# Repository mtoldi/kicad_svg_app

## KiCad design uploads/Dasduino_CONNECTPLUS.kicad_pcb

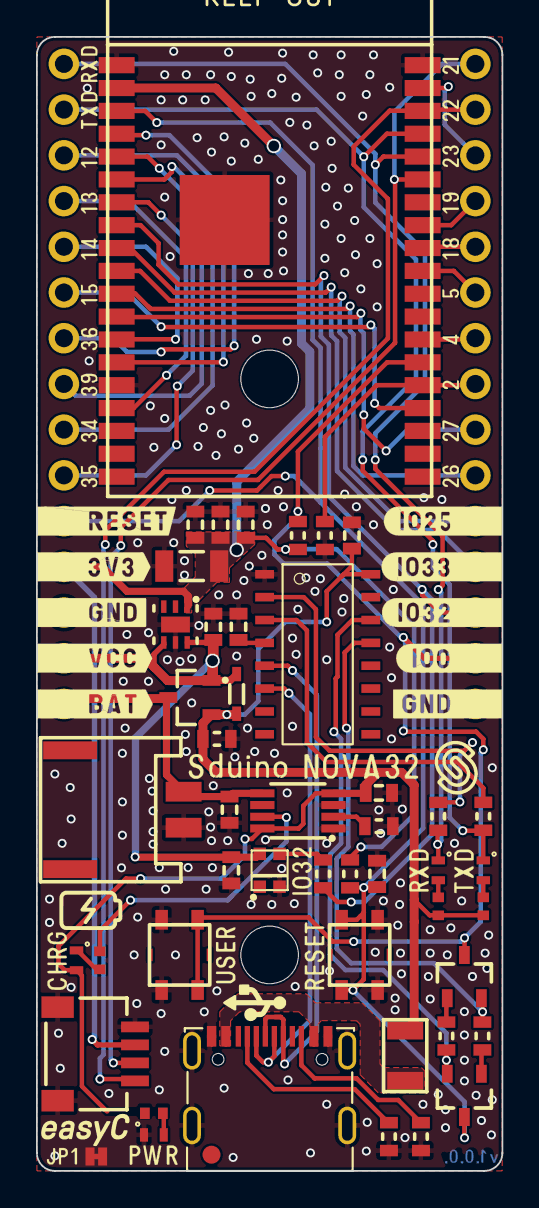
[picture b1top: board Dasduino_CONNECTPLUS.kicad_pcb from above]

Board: 2 copper layers, 25.9 x 63.0 mm, 51 parts (0 on the bottom side), 49 nets.

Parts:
C1: 10uF; 1206C
C2, C5, C11: 1uF; 0603C
C3, C4, C6: 0.1uF; 0603C
C7, C8, C9, C10: 2.2uF; 0603C
D1: blue; 0402LED
D2: orange; 0402LED
D3: purple; 0402LED
D4: WS2812B-2020
D5: schottky diode; SOD-323
D6: red; 0402LED
F1: 1206FUSE-500mA; 1206FUSE
FD1: Fiducial_Stencil; FIDUCIAL_1MM_PASTE
H1, H3: HOLE_3.2mm
K1: U262-161N-4BVC11
K2: easyC-SMD; easyC-connector
K3: JST-2pin-SMD
K4, K5: HEADER_MALE_15X1
Q1: PMOS-SOT-23-3; SOT-23-3
Q2, Q3: NPN-SOT-23-3; SOT-23-3
R1, R12, R13: 10k; 0603R
R2, R3: 5.1k; 0603R
R4, R5, R17: 1k; 0603R
R6, R7, R8, R15: 0R; 0402R
R9, R10, R11: 0603R
R14: 3k; 0603R
SW1, SW2: YTSA007A0151803B
U1: CH340C; SOP-16
U2: ESP32-WROVER
U3: TPS7A2633DRVR
U4: TP4056M; TP4056M-MSOP8

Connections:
+3V3: C1.2, C5.2, C6.2, C8.2, K2.3 (3V3), K4.4, R1.2, R13.2, U2.2 (VDD33), U3.1 (OUT)
D+: K1.A6 (DP1), K1.B6 (DP2), U1.5 (UD+)
D-: K1.A7 (DN1), K1.B7 (DN2), U1.6 (UD-)
DTR: Q3.2 (E), R10.1, U1.13 (DTR#)
GND: C1.1, C2.1, C3.1, C4.2, C5.1, C6.1, C7.1, C8.1, C9.1, C10.1, C11.2, D3.2 (K), D4.2 (GND), K1.A1 (GND), K1.A12 (GND), K1.B1 (GND), K1.B12 (GND), K1.SH (SHIELD), K2.4 (GND), K2.5 (SHIELD), K3.2 (-), K4.3, K5.1, R2.2, R3.2, R9.1, R12.1, R14.2, SW1.2, SW2.1, U1.1 (GND), U2.1 (GND), U2.15 (GND), U2.38 (GND), U2.39 (GND), U3.5 (GND), U4.1 (TEMP), U4.3 (GND)
IO0: K5.2, Q3.3 (C), R13.1, SW2.2, U2.25 (IO0)
IO2: K5.8, R12.2, U2.24 (IO2)
IO4: K5.9, U2.26 (IO4)
IO5: K5.10, U2.29 (IO5)
IO18: K5.11, U2.30 (IO18)
IO19: K5.12, U2.31 (IO19)
IO23: K5.13, U2.37 (IO23)
IO25: K5.5, U2.10 (IO25)
IO26: K5.6, U2.11 (IO26)
IO27: K5.7, U2.12 (IO27)
IO32: K5.3, R17.1, U2.8 (IO32)
IO33: K5.4, U2.9 (IO33)
IO34: K4.7, U2.6 (IO34)
IO35: K4.6, U2.7 (IO35)
unnamed: C4.1, U1.4 (V3)
unnamed: D1.1 (A), R6.1
unnamed: D2.1 (A), R7.1
unnamed: D3.1 (A), R8.2
unnamed: D4.3 (DI), R17.2
unnamed: D6.2 (K), R15.2
unnamed: F1.2, K1.A4 (VBUS), K1.A9 (VBUS), K1.B4 (VBUS), K1.B9 (VBUS)
unnamed: K1.A5 (CC1), R3.1
unnamed: K1.B5 (CC2), R2.1
unnamed: Q2.1 (B), R10.2
unnamed: Q3.1 (B), R11.2
unnamed: R4.1, U1.2 (TXD)
unnamed: R5.1, U1.3 (RXD)
unnamed: R14.1, U4.2 (PROG)
unnamed: R15.1, U4.7 (~CHRG)
RESET: C2.2, K4.5, Q2.3 (C), R1.1, SW1.1, U2.3 (EN)
RTS: Q2.2 (E), R11.1, U1.14 (RTS#)
RXD0: D2.2 (K), K4.15, R4.2, U2.34 (RXD0)
SCL: K2.1 (SCL), K5.14, U2.36 (IO22)
SDA: K2.2 (SDA), K5.15, U2.33 (IO21)
SENSOR_VN: K4.8, U2.5 (SENSOR_VN)
SENSOR_VP: K4.9, U2.4 (SENSOR_VP)
SPI_CS: K4.10, U2.23 (IO15)
SPI_MISO: K4.13, U2.14 (IO12)
SPI_MOSI: K4.12, U2.16 (IO13)
SPI_SCK: K4.11, U2.13 (IO14)
TXD0: D1.2 (K), K4.14, R5.2, U2.35 (TXD0)
VBAT: C9.2, K3.1 (+), K4.1, Q1.3 (D), U4.5 (BAT)
VCC: C7.2, C11.1, D4.4 (VDD), D5.2 (K), K4.2, Q1.2 (S), U3.4 (EN), U3.6 (IN)
VUSB: C3.2, C10.2, D5.1 (A), D6.1 (A), F1.1, Q1.1 (G), R6.2, R7.2, R8.1, R9.2, U1.16 (VCC), U4.4 (VCC), U4.8 (CE)

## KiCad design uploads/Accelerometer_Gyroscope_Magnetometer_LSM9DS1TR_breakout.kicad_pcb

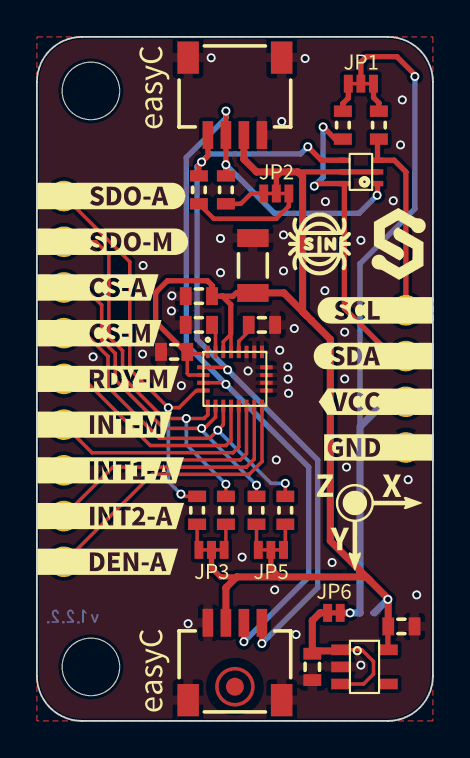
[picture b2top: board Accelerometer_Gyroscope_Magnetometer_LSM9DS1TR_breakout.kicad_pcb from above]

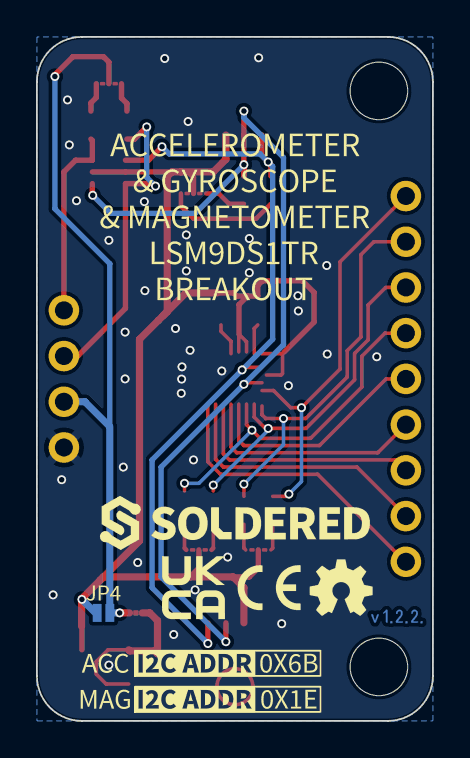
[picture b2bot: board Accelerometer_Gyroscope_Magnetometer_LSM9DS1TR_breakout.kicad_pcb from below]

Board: 2 copper layers, 22.0 x 38.0 mm, 59 parts (13 on the bottom side), 27 nets.

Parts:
C1, C2, C5: 100n; 0603C
C3: 10u; 1206C
C4: 10n; 0603C
C6, C7: 2u2; 0603C
FD1: FIDUCIAL; FIDUCIAL_23
H1, H2: HOLE_3.2mm
JP1, JP2, JP3, JP5: SMD_JUMPER_3_PAD_TRACE
JP4: SMD_JUMPER
JP6: SMD-JUMPER-CONNECTED_TRACE_SLODERMASK
K1: HEADER_MALE_9X1
K2, K4: easyC-SMD; easyC-connector
K3: HEADER_MALE_4X1
R1, R2, R3, R4, R5, R6, R7, R8: 10k; 0603R
U1: NMOS-DUAL; SOT-363
U2: LSM9DS1TR
U3: SE5218; SOT-23-5
kibuzzard-646B23F4: G***; kibuzzard-646B23F4
kibuzzard-6411B0B5: G***; kibuzzard-6411B0B5
kibuzzard-6411B0E0: G***; kibuzzard-6411B0E0
kibuzzard-6411B0F4: G***; kibuzzard-6411B0F4
kibuzzard-6411B1B6: G***; kibuzzard-6411B1B6
kibuzzard-6411B1E2: G***; kibuzzard-6411B1E2
kibuzzard-6411B1FF: G***; kibuzzard-6411B1FF
kibuzzard-6411B2B7: G***; kibuzzard-6411B2B7
kibuzzard-6411B2D2: G***; kibuzzard-6411B2D2
kibuzzard-6411B06B: G***; kibuzzard-6411B06B
kibuzzard-6411B07F: G***; kibuzzard-6411B07F
kibuzzard-6411B21F: G***; kibuzzard-6411B21F
kibuzzard-6411B22F: G***; kibuzzard-6411B22F
kibuzzard-6411B25F: G***; kibuzzard-6411B25F
kibuzzard-6411B32F: G***; kibuzzard-6411B32F
kibuzzard-6411B33C: G***; kibuzzard-6411B33C
kibuzzard-6411B059: G***; kibuzzard-6411B059
kibuzzard-6411B061: G***; kibuzzard-6411B061
kibuzzard-6411B074: G***; kibuzzard-6411B074
kibuzzard-6411B103: G***; kibuzzard-6411B103
kibuzzard-6411B119: G***; kibuzzard-6411B119
kibuzzard-6411B182: G***; kibuzzard-6411B182
kibuzzard-6411B196: G***; kibuzzard-6411B196
kibuzzard-6411B241: G***; kibuzzard-6411B241
kibuzzard-6411B292: G***; kibuzzard-6411B292
kibuzzard-6411B295: G***; kibuzzard-6411B295
kibuzzard-6411B327: G***; kibuzzard-6411B327
kibuzzard-6411B347: G***; kibuzzard-6411B347

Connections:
3V3: C1.2, C3.1, C5.2, C7.2, JP2.2, JP3.2, JP4.2, JP5.2, K2.3 (3V3), K4.3 (3V3), U1.2 (G2), U1.5 (G1), U2.1 (VDDIO), U2.3 (VDDIO), U2.22 (VDD), U2.23 (VDD), U3.5 (VOUT)
5V: JP1.2, JP4.1, JP6.2, K3.2
CS_AG: K1.3, R7.1, U2.7 (CS_AG)
CS_M: K1.4, R8.1, U2.8 (CS_M)
DEN_AG: K1.9, U2.13 (DEN_AG)
DRDY_M: K1.5, U2.9 (DRDY_M)
GND: C1.1, C2.2, C3.2, C4.2, C5.1, C6.1, C7.1, K2.4 (GND), K2.5 (SHIELD), K3.1, K4.4 (GND), K4.5 (SHIELD), U2.14 (RES), U2.15 (RES), U2.16 (RES), U2.17 (RES), U2.18 (RES), U2.19 (GND), U2.20 (GND), U3.2 (GND)
INT1_AG: K1.7, U2.11 (INT1_AG)
INT2_AG: K1.8, U2.12 (INT2_AG)
INT_M: K1.6, U2.10 (INT_M)
unnamed: C2.1, U2.24 (C1)
unnamed: C4.1, U2.21 (CAP)
unnamed: C6.2, JP6.1, U3.1 (VIN), U3.3 (EN)
unnamed: JP3.1, R6.2
unnamed: JP3.3, R5.2
unnamed: JP5.1, R8.2
unnamed: JP5.3, R7.2
SCL3,3: K2.1 (SCL), K4.1 (SCL), R4.1, U1.4 (S1), U2.2 (SCL)
SCL5: K3.4, R2.2, U1.3 (D1)
SCL_PULL3,3: JP2.1, R4.2
SCL_PULL5: JP1.1, R2.1
SDA3,3: K2.2 (SDA), K4.2 (SDA), R1.2, U1.1 (S2), U2.4 (SDA)
SDA5: K3.3, R3.1, U1.6 (D2)
SDA_PULL3,3: JP2.3, R1.1
SDA_PULL5: JP1.3, R3.2
SDO_AG: K1.1, R5.1, U2.5 (SDO_AG)
SDO_M: K1.2, R6.1, U2.6 (SDO_M)

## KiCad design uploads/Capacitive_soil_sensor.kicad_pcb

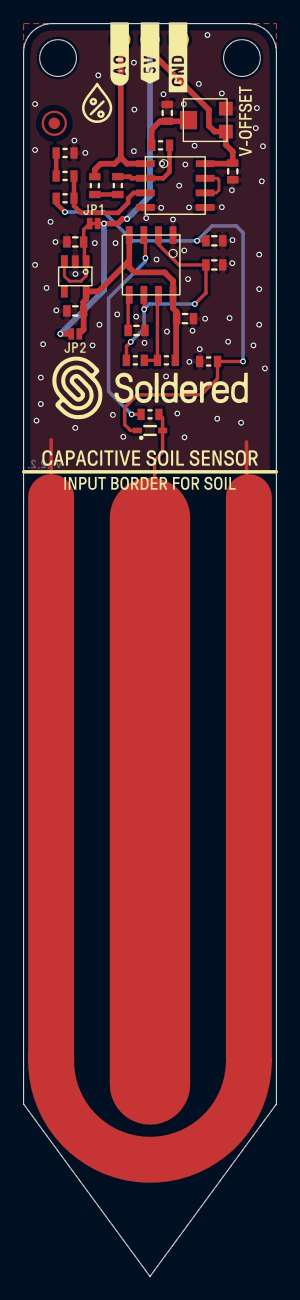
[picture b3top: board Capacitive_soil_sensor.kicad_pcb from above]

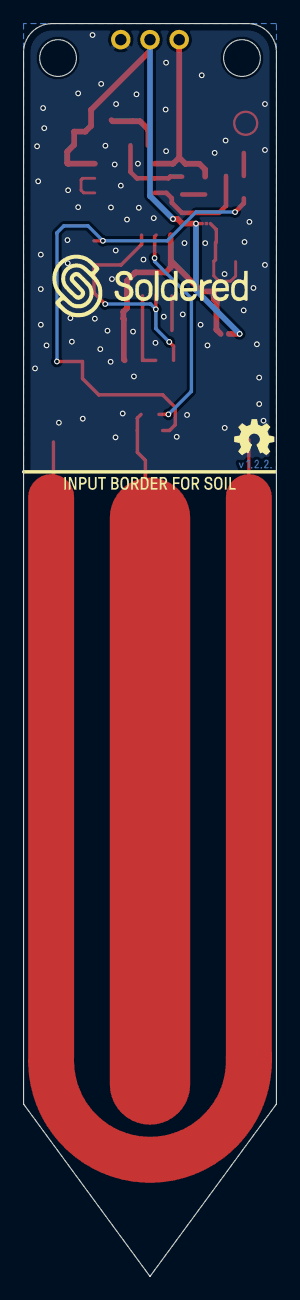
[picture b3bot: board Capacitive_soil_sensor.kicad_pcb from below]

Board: 2 copper layers, 22.0 x 109.0 mm, 33 parts (2 on the bottom side), 17 nets.

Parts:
C1: 1uF; 0603C
C2: 10nF; 0603C
C3: 0.01uF; 0603C
C4: 470pF; 0603C
C5, C6: 2.2uF; 0603C
C7, C8: 100n; 0603C
D1: BAT20J; SOD-323
FD1: FIDUCIAL; FIDUCIAL_23
H1, H2: HOLE_3.2mm
JP1: SMD-JUMPER-CONNECTED_TRACE_SLODERMASK
JP2: SMD_JUMPER
K1: HEADER_MALE_3X1
R1: 1M; 0603R
R2: 10K; 0603R
R3: 330R; 0603R
R4: 1K6; 0603R
R5, R9: 10k; 0603R
R6, R11: 47k; 0603R
R7, R10: 100k; 0603R
R8: tc33x-2-103e
U1: TLC555; SOIC−8
U2: SE5218; SOT-23-5
U3: MC33202DR2G; SOIC−8
kibuzzard-623B1C7E: G***; kibuzzard-623B1C7E
kibuzzard-6305B80A: G***; kibuzzard-6305B80A
kibuzzard-6305B93F, kibuzzard-6305B93F#2: G***; kibuzzard-6305B93F

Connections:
3V3: C3.2, C6.2, JP2.2, R3.2, U1.4 (RESET), U1.8 (VDD), U2.5 (VOUT)
5V: C8.1, JP1.2, JP2.1, K1.2, R8.1, U3.8 (V+)
/Out: K1.1, R11.2, U3.1
/Vsen: C1.1, D1.2 (K), R1.1, R5.1
GND: C1.2, C2.1, C3.1, C4.1, C5.1, C6.1, C7.2, C8.2, K1.3, R1.2, R7.1, R8.3, U1.1 (GND), U2.2 (GND), U3.4 (V-), U3.5 (+)
unnamed: C2.2, U1.5 (CONT)
unnamed: C4.2, R4.2, U1.2 (TRIG), U1.6 (THRES)
unnamed: C5.2, JP1.1, U2.1 (VIN), U2.3 (EN)
unnamed: C7.1, R8.2, R9.1
unnamed: D1.1 (A), R2.1
unnamed: R2.2, U1.3 (OUT)
unnamed: R3.1, R4.1, U1.7 (DISCH)
unnamed: R5.2, R6.2, U3.3 (+)
unnamed: R6.1, R7.2
unnamed: R9.2, R10.1, U3.2 (-)
unnamed: R10.2, R11.1
unnamed: U3.6 (-), U3.7

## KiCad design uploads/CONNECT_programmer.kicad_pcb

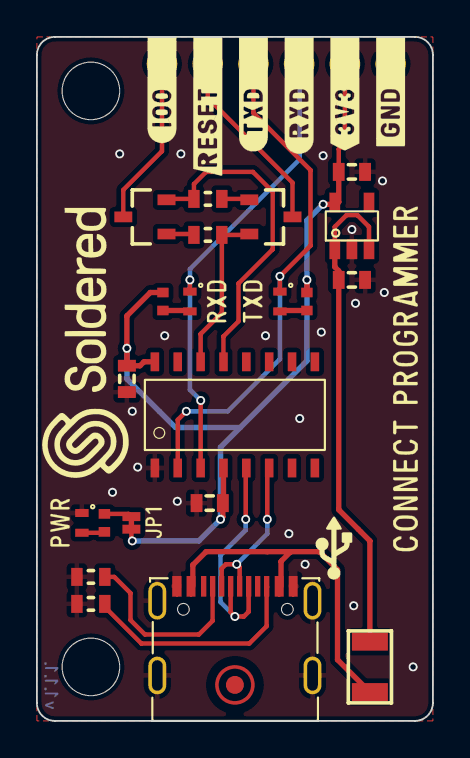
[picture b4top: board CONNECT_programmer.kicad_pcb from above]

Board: 2 copper layers, 22.0 x 38.0 mm, 25 parts (1 on the bottom side), 20 nets.

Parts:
C1, C2: 0.1uF; 0603C
C3, C4: 2.2uF; 0603C
D1: white; 0402LED
D2: blue; 0402LED
D3: purple; 0402LED
F1: 1206FUSE-500mA; 1206FUSE
FD1: FIDUCIAL; FIDUCIAL_23
H1, H2: HOLE_3.2mm
JP1: SMD-JUMPER-CONNECTED_TRACE_SLODERMASK
K1: U262-161N-4BVC11
K2: NOVA_programmer_header; HEADER_MALE_6X1
Q1, Q2: NPN-SOT-23-3; SOT-23-3
R1, R2: 5.1k; 0603R
R3, R4: 10k; 0402R
R5: 2k2; 0402R
R6, R7: 10k; 0603R
U1: CH340C; SOP-16
U2: SE5218; SOT-23-5

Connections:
+3V3: C1.2, C2.1, C4.2, JP1.1, K2.2 (VCC), R3.2, R4.2, U1.4 (V3), U1.16 (VCC), U2.5 (VOUT)
D+: K1.A6 (DP1), K1.B6 (DP2), U1.5 (UD+)
D-: K1.A7 (DN1), K1.B7 (DN2), U1.6 (UD-)
DTR: Q2.2 (E), R6.1, U1.13 (DTR#)
GND: C1.1, C2.2, C3.1, C4.1, D3.2 (K), K1.A1 (GND), K1.A12 (GND), K1.B1 (GND), K1.B12 (GND), K1.SH (SHIELD), K2.1 (GND), R1.2, R2.2, U1.1 (GND), U2.2 (GND)
IO0: K2.6 (GPIO0), Q2.3 (C)
unnamed: D1.1 (A), R3.1
unnamed: D2.1 (A), R4.1
unnamed: D3.1 (A), R5.2
unnamed: F1.2, K1.A4 (VBUS), K1.A9 (VBUS), K1.B4 (VBUS), K1.B9 (VBUS)
unnamed: JP1.2, R5.1
unnamed: K1.A5 (CC1), R2.1
unnamed: K1.B5 (CC2), R1.1
unnamed: Q1.1 (B), R6.2
unnamed: Q2.1 (B), R7.2
RESET: K2.5 (RESET), Q1.3 (C)
RTS: Q1.2 (E), R7.1, U1.14 (RTS#)
RXD0: D2.2 (K), K2.3 (TX), U1.3 (RXD)
TXD0: D1.2 (K), K2.4 (RX), U1.2 (TXD)
VUSB: C3.2, F1.1, U2.1 (VIN), U2.3 (EN)

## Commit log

2025-07-08 first version
2025-07-08 working version
2025-07-08 added download
2025-07-08 soldered purple
2025-07-08 preuzimanje sa unesenim sku-om
